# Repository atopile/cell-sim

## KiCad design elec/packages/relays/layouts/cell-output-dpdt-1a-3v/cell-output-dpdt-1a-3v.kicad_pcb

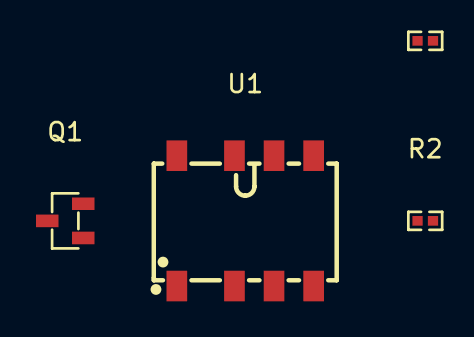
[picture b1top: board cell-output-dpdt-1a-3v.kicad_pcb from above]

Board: 2 copper layers, 4 parts (0 on the bottom side), 4 nets, no tracks yet.

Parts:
Q1: SOT-23-3_L2.9-W1.3-P1.90-LS2.4-BR
R1, R2: 10kΩ; R0402
U1: RELAY-SMD_G6K-2F-Y

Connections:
drain: Q1.3, U1.8
gate: Q1.1, R2.2
line: R1.1, R2.1
lv: Q1.2, R1.2

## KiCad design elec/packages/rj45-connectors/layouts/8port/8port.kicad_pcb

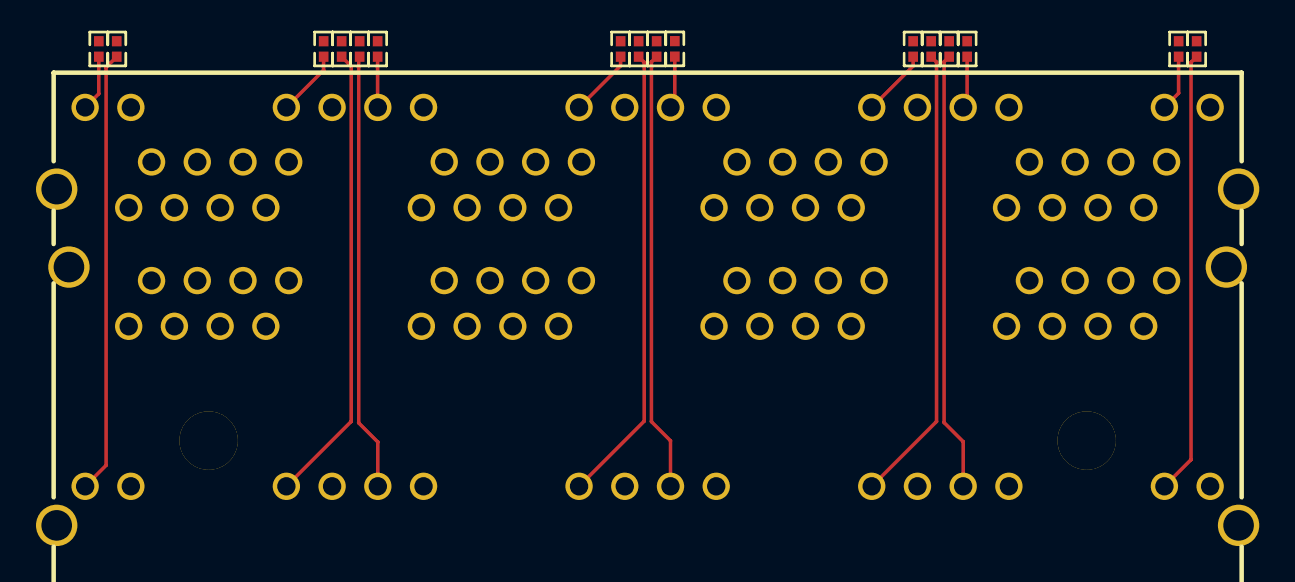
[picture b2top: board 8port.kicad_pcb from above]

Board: 2 copper layers, 17 parts (0 on the bottom side), 17 nets.

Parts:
R1, R2, R3, R4, R5, R6, R7, R8, R9, R10, R11, R12, R13, R14, R15, R16: 470Ω; R0402
U1: RJ45-TH_HC-RJ45-059C-2X4-1

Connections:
10: R9.2, U1.10
12: R1.2, U1.12
22: R10.2, U1.22
24: R2.2, U1.24
34: R11.2, U1.34
36: R3.2, U1.36
46: R12.2, U1.46
48: R4.2, U1.48
57: R5.2, U1.57
59: R13.2, U1.59
69: R6.2, U1.69
71: R14.2, U1.71
81: R7.2, U1.81
83: R15.2, U1.83
93: R8.2, U1.93
95: R16.2, U1.95
lv: U1.9, U1.11, U1.21, U1.23, U1.33, U1.35, U1.45, U1.47, U1.58, U1.60, U1.70, U1.72, U1.82, U1.84, U1.94, U1.96, U1.97, U1.98, U1.99, U1.100, U1.101, U1.102

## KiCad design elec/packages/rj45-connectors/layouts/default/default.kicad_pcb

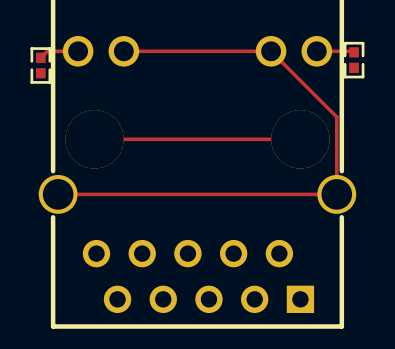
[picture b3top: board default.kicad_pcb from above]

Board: 2 copper layers, 3 parts (0 on the bottom side), 3 nets.

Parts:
R1, R2: 470.0Ω; R0402
U1: RJ45-TH_HR911130A

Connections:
11: R2.2, U1.11
14: R1.2, U1.14
lv: U1.12, U1.13, U1.SHIELD0, U1.SHIELD1
